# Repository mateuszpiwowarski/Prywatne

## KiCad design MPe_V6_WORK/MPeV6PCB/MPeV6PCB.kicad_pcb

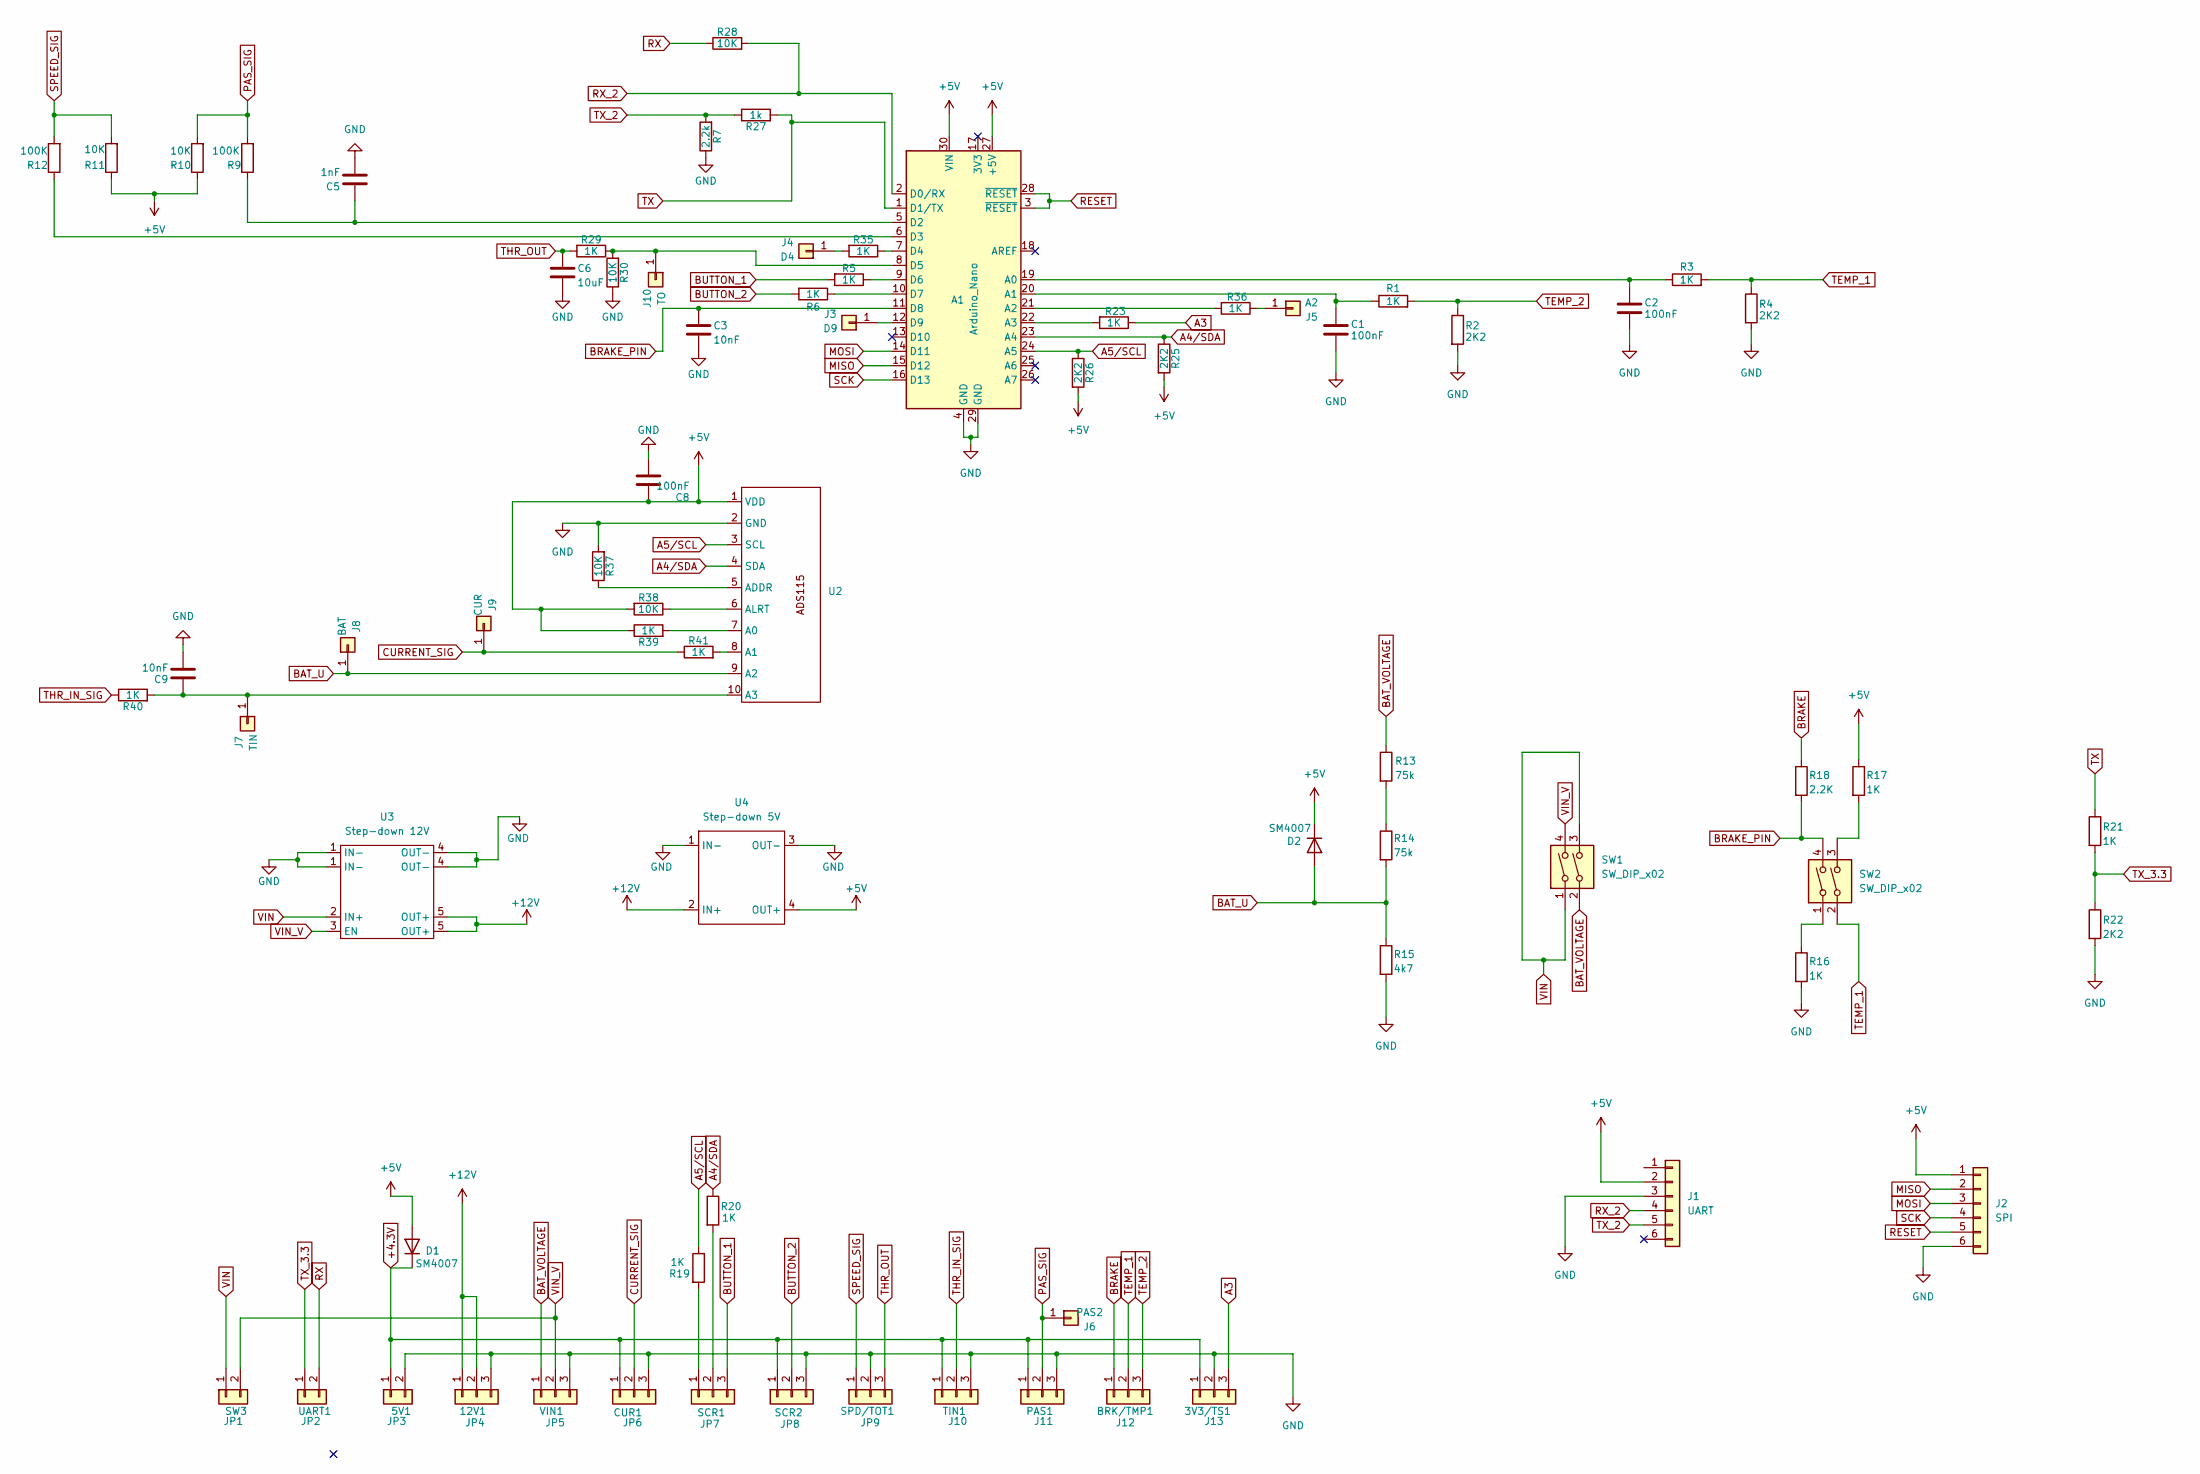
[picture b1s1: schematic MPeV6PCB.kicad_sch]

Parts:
3V3/TS1: J13; DG30825403P1400AH
5V1: JP3; DG30825402P1400AH
12V1: JP4; DG30825403P1400AH
A1: Arduino_Nano
BRK/TMP1: J12; DG30825403P1400AH
C1, C2, C8: 100nF; C_0603_1608Metric_Pad1.08x0.95mm_HandSolder
C3, C9: 10nF; C_0603_1608Metric_Pad1.08x0.95mm_HandSolder
C5: 1nF; C_0603_1608Metric_Pad1.08x0.95mm_HandSolder
C6: 10uF; C_0603_1608Metric_Pad1.08x0.95mm_HandSolder
CUR1: JP6; DG30825403P1400AH
D1, D2: SM4007; D_MELF
J1: UART; TerminalBlock_Xinya_XY308-2.54-6P_1x06_P2.54mm_Horizontal
J2: SPI; TerminalBlock_Xinya_XY308-2.54-6P_1x06_P2.54mm_Horizontal
J3: D9; HOLE
J4: D4; HOLE
J5: A2; HOLE
J6: PAS2; HOLE
J7: TIN; HOLE
J8: BAT; HOLE
J9: CUR; HOLE
J10: TO; HOLE
PAS1: J11; DG30825403P1400AH
R1, R3, R5, R6, R16, R17, R19, R20, R21, R23, R29, R35, R36, R39, R40, R41: 1K; R_0805_2012Metric_Pad1.20x1.40mm_HandSolder
R2, R4, R22, R25, R26: 2K2; R_0805_2012Metric_Pad1.20x1.40mm_HandSolder
R7: 2.2k; R_0805_2012Metric_Pad1.20x1.40mm_HandSolder
R9, R12: 100K; R_0805_2012Metric_Pad1.20x1.40mm_HandSolder
R10, R11, R28, R30, R37, R38: 10K; R_0805_2012Metric_Pad1.20x1.40mm_HandSolder
R13, R14: 75k; R_0805_2012Metric_Pad1.20x1.40mm_HandSolder
R15: 4k7; R_0805_2012Metric_Pad1.20x1.40mm_HandSolder
R18: 2.2K; R_0805_2012Metric_Pad1.20x1.40mm_HandSolder
R27: 1k; R_0805_2012Metric_Pad1.20x1.40mm_HandSolder
SCR1: JP7; DG30825403P1400AH
SCR2: JP8; DG30825403P1400AH
SPD/TOT1: JP9; DG30825403P1400AH
SW1, SW2: SW_DIP_x02; SW_DIP_SPSTx02_Slide_9.78x7.26mm_W7.62mm_P2.54mm
SW3: JP1; DG30825402P1400AH
TIN1: J10; DG30825403P1400AH
U2: ADS1115PCB
U3: Step-down 12V; 12V Step-Down
U4: Step-down 5V; 5V Step-Down
UART1: JP2; DG30825402P1400AH
VIN1: JP5; DG30825403P1400AH

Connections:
+4.3V: 3V3/TS1.1, 5V1.1, CUR1.1, D1.1 (K), PAS1.1, SCR2.1, TIN1.1
+5V: A1.27 (+5V), A1.30 (VIN), C8.1, D1.2 (A), D2.1 (K), J1.2, J2.1, R10.1, R11.1, R17.1, R25.2, R26.2, R38.2, R39.1, U2.1 (VDD), U4.4 (OUT+)
+12V: 12V1.1, 12V1.2, U3.5 (OUT+), U4.2 (IN+)
A3: 3V3/TS1.3, R23.1
A4/SDA: A1.23 (A4), R20.1, R25.1, U2.4 (SDA)
A5/SCL: A1.24 (A5), R19.1, R26.1, U2.3 (SCL)
BAT_U: D2.2 (A), J8.1, R14.2, R15.1, U2.9 (A2)
BAT_VOLTAGE: R13.1, SW1.2, VIN1.1
BRAKE: BRK/TMP1.1, R18.1
BRAKE_PIN: A1.11 (D8), C3.1, R18.2, SW2.4
BUTTON_1: R5.2, SCR1.3
BUTTON_2: R6.2, SCR2.2
CURRENT_SIG: CUR1.2, J9.1, R41.1
GND: 3V3/TS1.2, 5V1.2, 12V1.3, A1.4 (GND), A1.29 (GND), C1.2, C2.2, C3.2, C5.2, C6.2, C8.2, C9.2, CUR1.3, J1.3, J2.6, PAS1.3, R2.2, R4.2, R7.1, R15.2, R16.2, R22.2, R30.1, R37.2, SCR2.3, SPD/TOT1.2, TIN1.3, U2.2 (GND), U3.1 (IN-), U3.4 (OUT-), U4.1 (IN-), U4.3 (OUT-), VIN1.3
MISO: A1.15 (D12), J2.2
MOSI: A1.14 (D11), J2.3
unnamed: A1.19 (A0), C2.1, R3.1
unnamed: A1.20 (A1), C1.1, R1.1
unnamed: A1.21 (A2), R36.2
unnamed: A1.22 (A3), R23.2
unnamed: A1.5 (D2), C5.1, R9.1
unnamed: A1.6 (D3), R12.1
unnamed: A1.7 (D4), R35.1
unnamed: A1.8 (D5), J10.1, R29.1, R30.2
unnamed: A1.9 (D6), R5.1
unnamed: A1.10 (D7), R6.1
unnamed: A1.12 (D9), J3.1
unnamed: J4.1, R35.2
unnamed: J5.1, R36.1
unnamed: C9.1, J7.1, R40.2, U2.10 (A3)
unnamed: R13.2, R14.1
unnamed: R16.1, SW2.1
unnamed: R17.2, SW2.3
unnamed: R19.2, SCR1.1
unnamed: R20.2, SCR1.2
unnamed: R39.2, U2.7 (A0)
unnamed: R41.2, U2.8 (A1)
unnamed: R37.1, U2.5 (ADDR)
unnamed: R38.1, U2.6 (ALRT)
PAS_SIG: J6.1, PAS1.2, R9.2, R10.2
RESET: A1.3 (~RESET), A1.28 (~RESET), J2.5
RX: R28.1, UART1.2
RX_2: A1.2 (D0/RX), J1.4, R28.2
SCK: A1.16 (D13), J2.4
SPEED_SIG: R11.2, R12.2, SPD/TOT1.1
TEMP_1: BRK/TMP1.2, R3.2, R4.1, SW2.2
TEMP_2: BRK/TMP1.3, R1.2, R2.1
THR_IN_SIG: R40.1, TIN1.2
THR_OUT: C6.1, R29.2, SPD/TOT1.3
TX: A1.1 (D1/TX), R21.1, R27.2
TX_2: J1.5, R7.2, R27.1
TX_3.3: R21.2, R22.1, UART1.1
VIN: SW1.1, SW1.3, SW3.1, U3.2 (IN+)
VIN_V: SW1.4, SW3.2, U3.3 (EN), VIN1.2

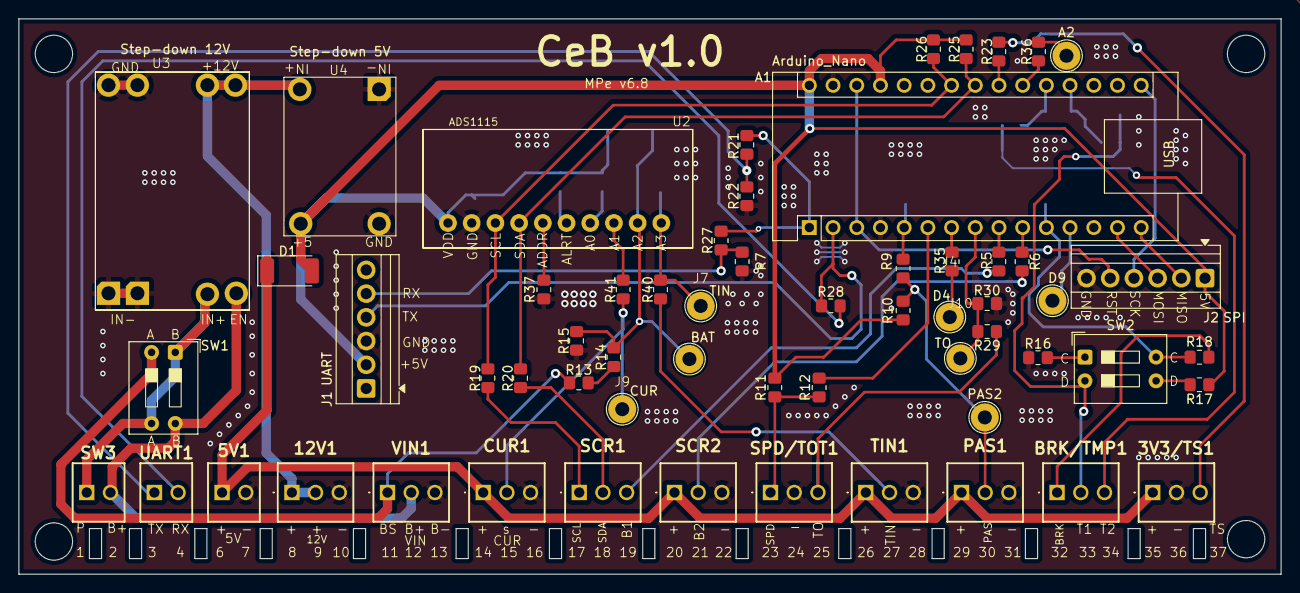
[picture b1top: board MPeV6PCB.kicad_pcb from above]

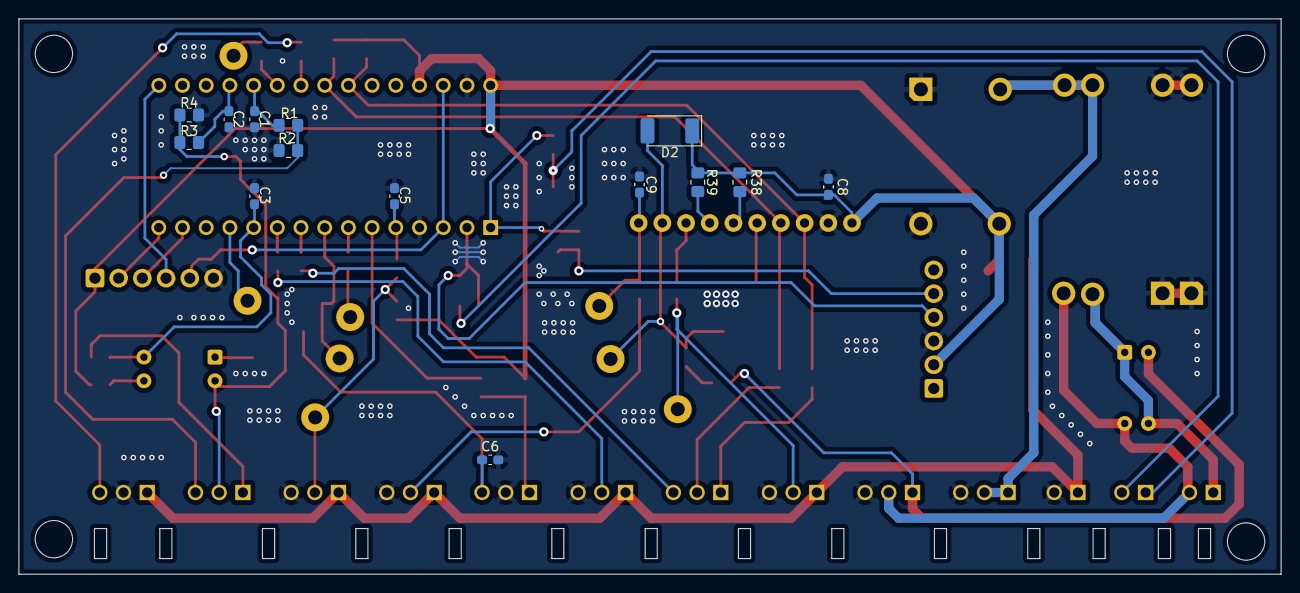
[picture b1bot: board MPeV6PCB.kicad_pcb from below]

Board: 2 copper layers, 135.2 x 59.5 mm, 73 parts (14 on the bottom side), 54 nets.

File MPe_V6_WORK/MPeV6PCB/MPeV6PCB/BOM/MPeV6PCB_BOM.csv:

"sep=;"
Id;Designator;Footprint;Quantity;Value;Supplier and ref
1;3V3/TS1;SamacSys_Parts:DG30825403P1400AH;1;J13;
2;5V1;SamacSys_Parts:DG30825402P1400AH;1;JP3;
3;12V1;SamacSys_Parts:DG30825403P1400AH;1;JP4;
4;A1;Module:Arduino_Nano;1;Arduino_Nano;
5;BRK/TMP1;SamacSys_Parts:DG30825403P1400AH;1;J12;
6;C1,C2,C8;Capacitor_SMD:C_0603_1608Metric_Pad1.08x0.95mm_HandSolder;3;100nF;
7;C3,C9;Capacitor_SMD:C_0603_1608Metric_Pad1.08x0.95mm_HandSolder;2;10nF;
8;C5;Capacitor_SMD:C_0603_1608Metric_Pad1.08x0.95mm_HandSolder;1;1nF;
9;C6;Capacitor_SMD:C_0603_1608Metric_Pad1.08x0.95mm_HandSolder;1;10uF;
10;CUR1;SamacSys_Parts:DG30825403P1400AH;1;JP6;
11;D1,D2;Diode_SMD:D_MELF;2;SM4007;
12;J1;TerminalBlock:TerminalBlock_Xinya_XY308-2.54-6P_1x06_P2.54mm_Horizontal;1;UART;
13;J2;TerminalBlock:TerminalBlock_Xinya_XY308-2.54-6P_1x06_P2.54mm_Horizontal;1;SPI;
14;J3;New_Library_Footprint:HOLE;1;D9;
15;J4;New_Library_Footprint:HOLE;1;D4;
16;J5;New_Library_Footprint:HOLE;1;A2;
17;J6;New_Library_Footprint:HOLE;1;PAS2;
18;J7;New_Library_Footprint:HOLE;1;TIN;
19;J8;New_Library_Footprint:HOLE;1;BAT;
20;J9;New_Library_Footprint:HOLE;1;CUR;
21;J10;New_Library_Footprint:HOLE;1;TO;
22;PAS1;SamacSys_Parts:DG30825403P1400AH;1;J11;
23;R1,R3,R5,R6,R16,R17,R19-R21,R23,R29,R35,R36,R39-R41;Resistor_SMD:R_0805_2012Metric_Pad1.20x1.40mm_HandSolder;16;1K;
24;R2,R4,R22,R25,R26;Resistor_SMD:R_0805_2012Metric_Pad1.20x1.40mm_HandSolder;5;2K2;
25;R7;Resistor_SMD:R_0805_2012Metric_Pad1.20x1.40mm_HandSolder;1;2.2k;
26;R9,R12;Resistor_SMD:R_0805_2012Metric_Pad1.20x1.40mm_HandSolder;2;100K;
27;R10,R11,R28,R30,R37,R38;Resistor_SMD:R_0805_2012Metric_Pad1.20x1.40mm_HandSolder;6;10K;
28;R13,R14;Resistor_SMD:R_0805_2012Metric_Pad1.20x1.40mm_HandSolder;2;75k;
29;R15;Resistor_SMD:R_0805_2012Metric_Pad1.20x1.40mm_HandSolder;1;4k7;
30;R18;Resistor_SMD:R_0805_2012Metric_Pad1.20x1.40mm_HandSolder;1;2.2K;
31;R27;Resistor_SMD:R_0805_2012Metric_Pad1.20x1.40mm_HandSolder;1;1k;
32;SCR1;SamacSys_Parts:DG30825403P1400AH;1;JP7;
33;SCR2;SamacSys_Parts:DG30825403P1400AH;1;JP8;
34;SPD/TOT1;SamacSys_Parts:DG30825403P1400AH;1;JP9;
35;SW1,SW2;Button_Switch_THT:SW_DIP_SPSTx02_Slide_9.78x7.26mm_W7.62mm_P2.54mm;2;SW_DIP_x02;
36;SW3;SamacSys_Parts:DG30825402P1400AH;1;JP1;
37;TIN1;SamacSys_Parts:DG30825403P1400AH;1;J10;
38;U2;New_Library_Footprint:ADS1115PCB;1;~;
39;U3;New_Library_Footprint:12V Step-Down;1;Step-down 12V;
40;U4;New_Library_Footprint:5V Step-Down;1;Step-down 5V;
41;UART1;SamacSys_Parts:DG30825402P1400AH;1;JP2;
42;VIN1;SamacSys_Parts:DG30825403P1400AH;1;JP5;

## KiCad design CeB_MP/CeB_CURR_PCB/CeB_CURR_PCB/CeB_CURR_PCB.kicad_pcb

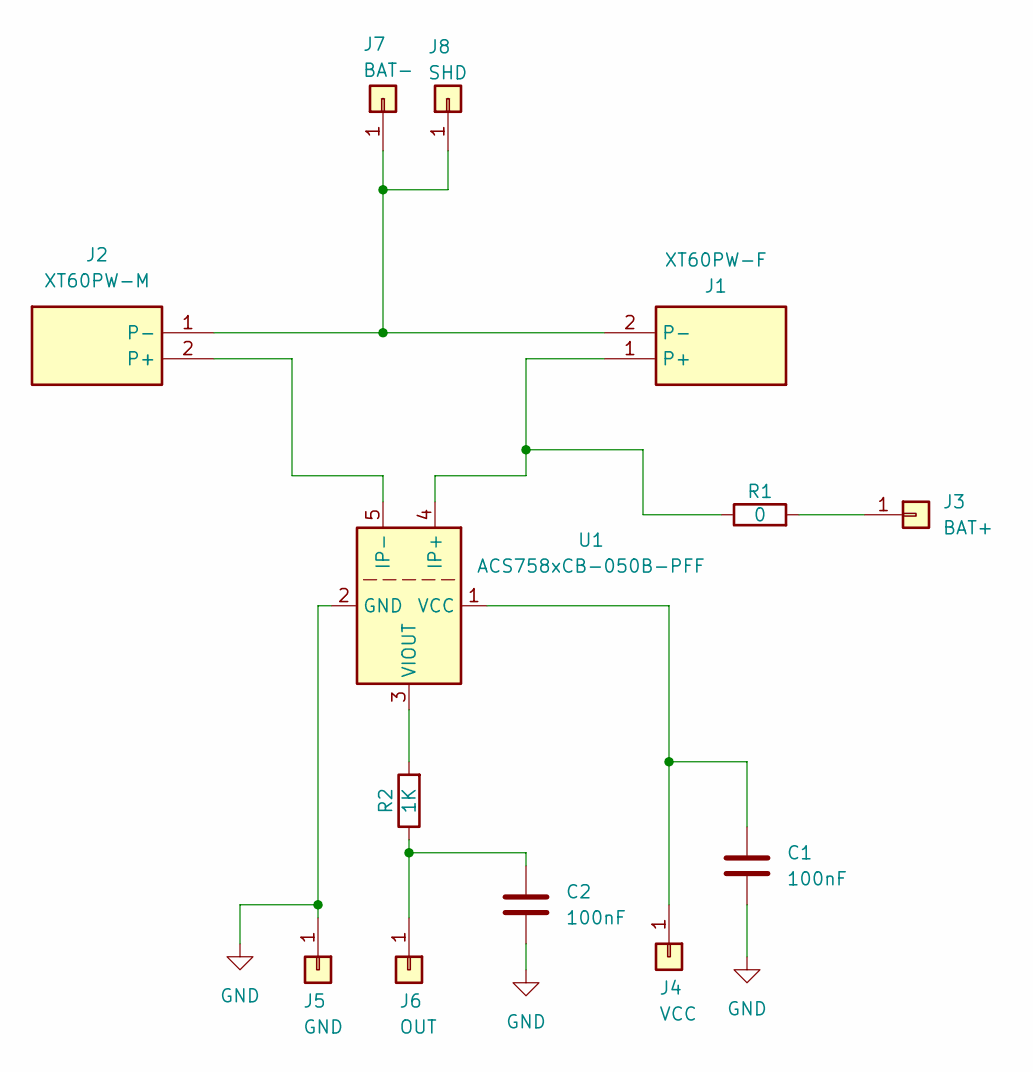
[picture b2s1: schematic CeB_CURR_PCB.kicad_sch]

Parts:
C1, C2: 100nF; C_0603_1608Metric_Pad1.08x0.95mm_HandSolder
J1: XT60PW-F; XT60PWF; Manufacturer_Part_Number XT60PW-F
J2: XT60PW-M; XT60PWM; Manufacturer_Part_Number XT60PW-M
J3: BAT+; HOLE
J4: VCC; HOLE
J5: GND; HOLE
J6: OUT; HOLE
J7: BAT-; HOLE
J8: SHD; HOLE
R1: 0; R_0603_1608Metric_Pad0.98x0.95mm_HandSolder
R2: 1K; R_0603_1608Metric_Pad0.98x0.95mm_HandSolder
U1: ACS758xCB-050B-PFF; Allegro_CB_PFF

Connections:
GND: C1.2, C2.2, J5.1, U1.2 (GND)
unnamed: J1.1 (P+), R1.1, U1.4 (IP+)
unnamed: J1.2 (P-), J2.1 (P-), J7.1, J8.1
unnamed: J2.2 (P+), U1.5 (IP-)
unnamed: J3.1, R1.2
unnamed: C1.1, J4.1, U1.1 (VCC)
unnamed: C2.1, J6.1, R2.1
unnamed: R2.2, U1.3 (VIOUT)

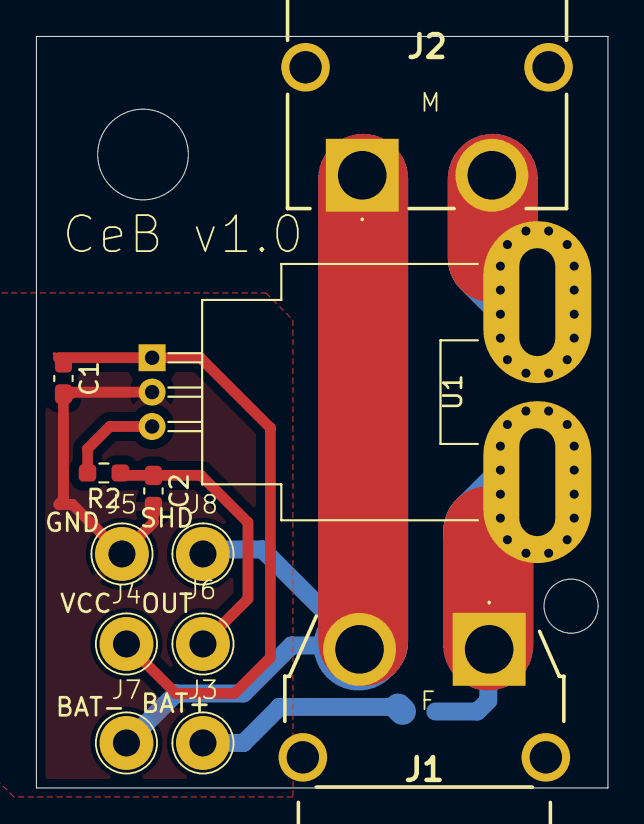
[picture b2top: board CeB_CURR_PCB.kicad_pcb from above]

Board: 2 copper layers, 31.8 x 41.8 mm, 13 parts (1 on the bottom side), 8 nets.

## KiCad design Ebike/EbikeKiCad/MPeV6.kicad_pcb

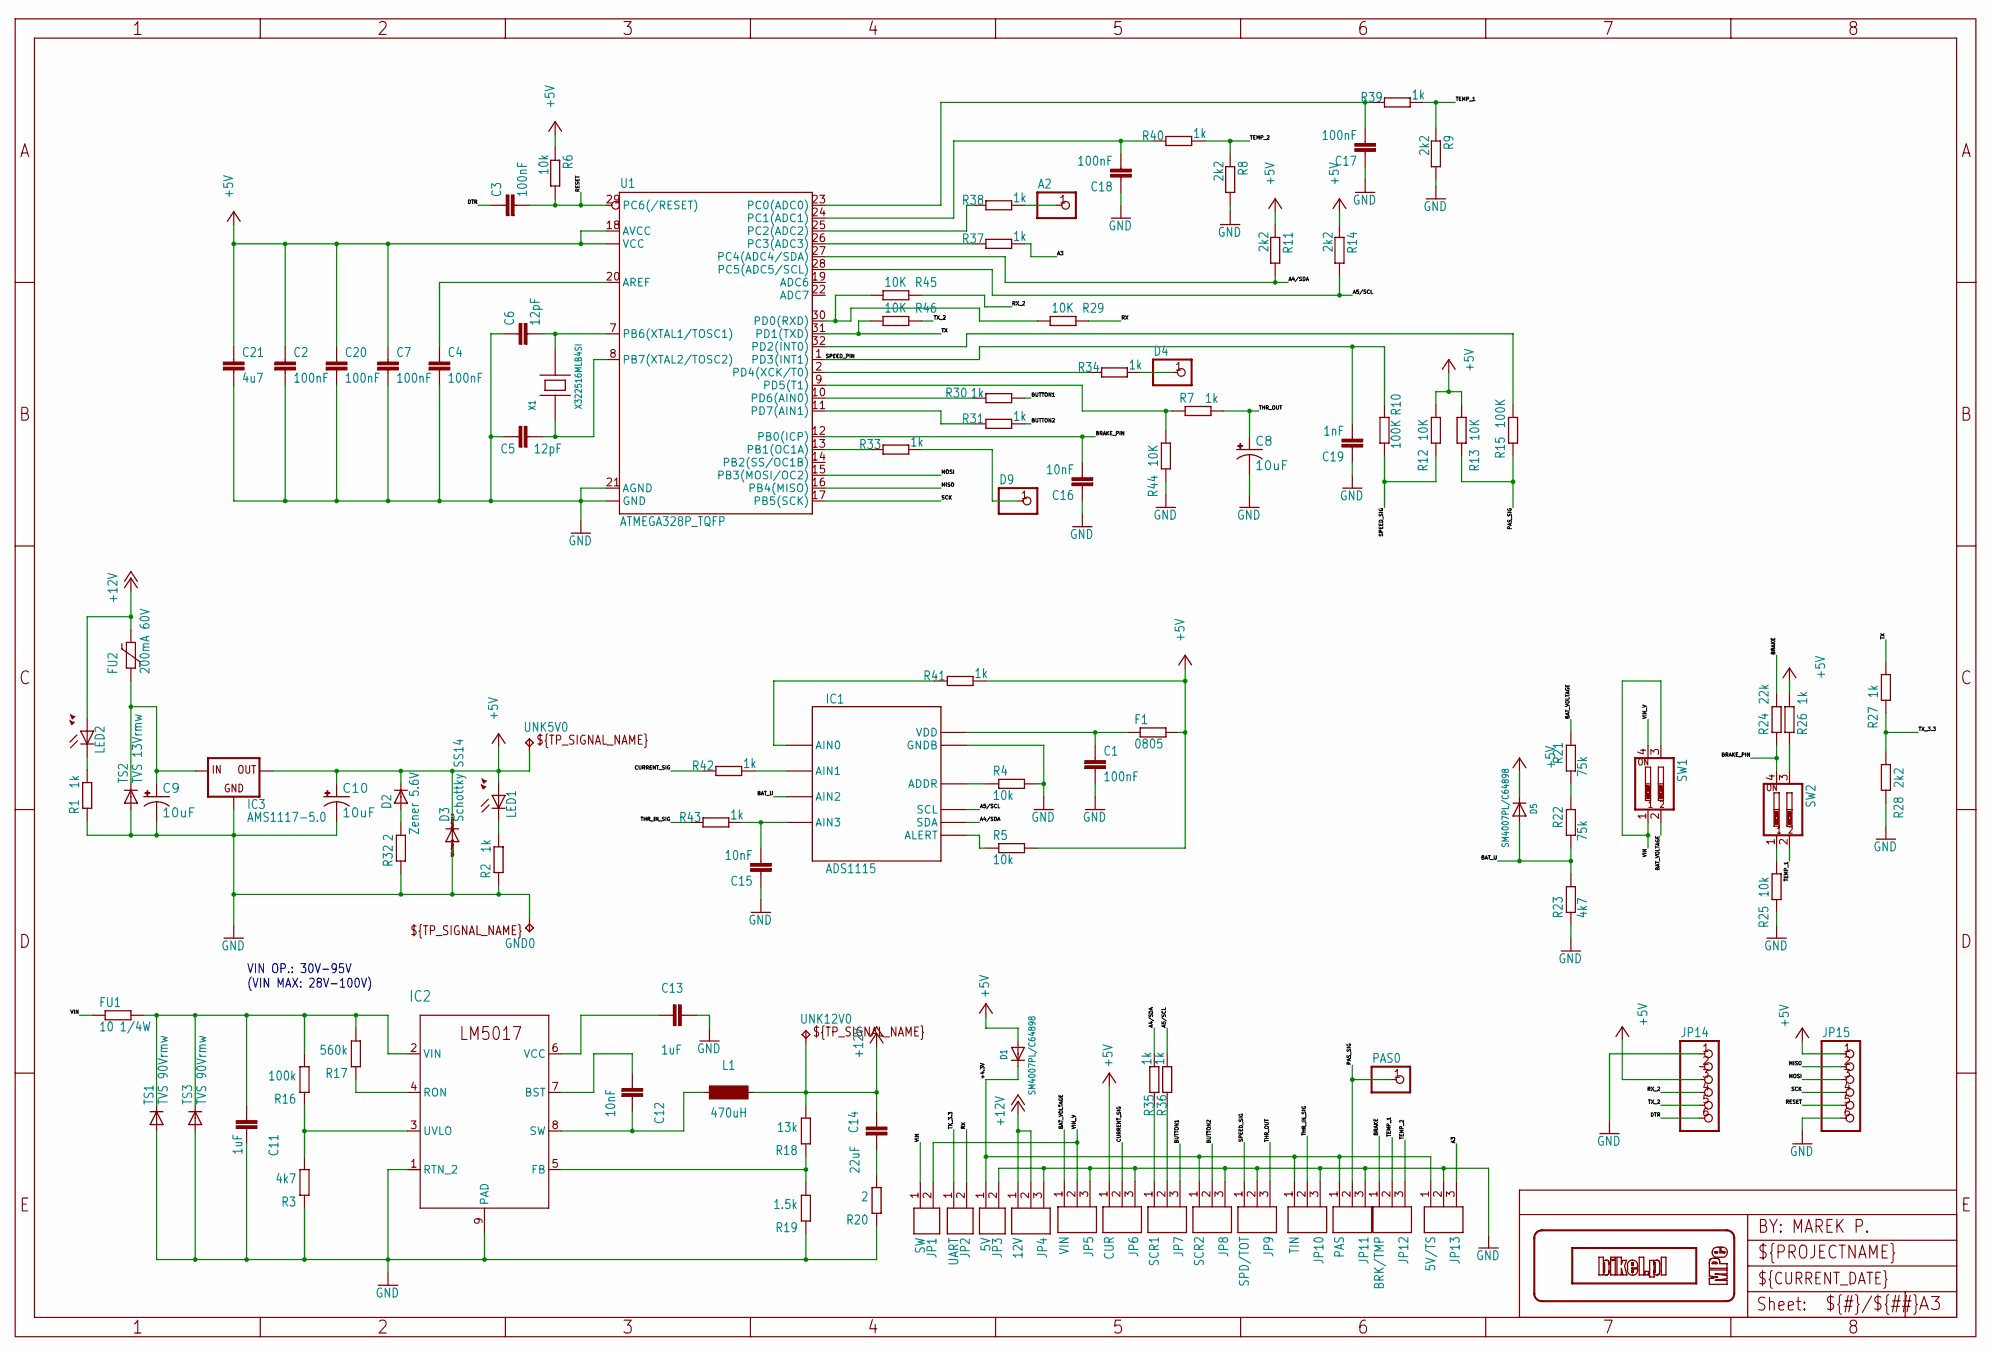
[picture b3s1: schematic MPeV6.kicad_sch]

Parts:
A2: PINHD-1X1; 1X01
C1, C2, C3, C4, C7, C17, C18, C20: 100nF; C0603
C5, C6: 12pF; C0603
C8, C9, C10: 10uF; EIA3216
C11: 1uF; C1206
C12: 10nF; C0805
C13: 1uF; C0603
C14: 22uF; C0805
C15, C16: 10nF; C0603
C19: 1nF; C0603
C21: 4u7; C0603
D1, D5: SM4007PL/C64898; SOD-123
D2: Zener 5.6V; MELF-MLL34
D3: Schottky SS14; DO-214AC
D4, D9: PINHD-1X1; 1X01
F1: 0805; R0805
FU1: 10 1/4W; 0204_7
FU2: 200mA 60V; 1812L
GND0: TP_5V; P1-13
IC1: ADS1115; MSOP10_0.5
IC2: LM5017MR/NOPB; MRA08A
IC3: AMS1117-5.0; SOT223
JP1: SW; ARK254-PB+
JP2: UART; ARK254-2-COM
JP3: 5V; ARK254-2-5V
JP4: 12V; ARK254-3-12V-EL
JP5: VIN; ARK254-3-VIN
JP6: CUR; ARK254-3+S-
JP7: SCR1; ARK254-3
JP8: SCR2; ARK254-3
JP9: SPD/TOT; ARK254-3-SPD-TOT
JP10: TIN; ARK254-3+S-
JP11: PAS; ARK254-3+S-
JP12: BRK/TMP; ARK254-3-BRK-TMP
JP13: 5V/TS; ARK254-3-5V-TS
JP14, JP15: PINHD-1X6; 1X06
L1: 470uH; SLF12555T-102MR34-PF; LCSC C13738
LED1, LED2: LEDCHIP-LED0805; CHIP-LED0805
PAS0: PINHD-1X1; 1X01
R1, R2, R7, R26, R27, R30, R31, R33, R34, R35, R36, R37, R38, R39, R40, R41, R42, R43: 1k; R0603
R3: 4k7; R0603
R4, R5, R6, R25: 10k; R0603
R8, R9, R11, R14, R28: 2k2; R0603
R10, R15: 100K; R0603
R12, R13, R29, R44, R45, R46: 10K; R0603
R16: 100k; R0603
R17: 560k; R0603
R18: 13k; R0603
R19: 1.5k; R0603
R20, R32: 2; R0805
R21, R22: 75k; R0805
R23: 4k7; R0805
R24: 22k; R0603
SW1, SW2: SW_DIP-2; EDG-02
TS1, TS3: TVS 90Vrmw; DO214AA
TS2: TVS 13Vrmw; DO214AA
U1: ATMEGA328P_TQFP; TQFP32-08
UNK5V0, UNK12V0: TP_5V; P1-13
X1: X322516MLB4SI; IQG3225

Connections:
3: IC2.5 (FB), R18.2, R19.1
6: C13.2, IC2.6 (VCC)
7: IC2.4 (RON), R17.2
9: C14.2, R20.1
12V_FUSED: C9.+, FU2.2, IC3.3 (IN), TS2.C
+4.3V: D1.C, JP3.1, JP8.1, JP10.1, JP11.1, JP13.1
+5V: C2.1, C7.1, C10.+, C20.1, C21.1, D1.A, D2.1 (C), D3.C, D5.C, F1.2, IC3.2 (OUT), IC3.4 (OUT), JP6.1, JP14.3, JP15.1, LED1.A, R5.2, R6.1, R11.1, R12.2, R13.2, R14.1, R26.2, R41.1, U1.4 (VCC), U1.6 (VCC), U1.18 (AVCC), UNK5V0.TP; also elsewhere on the board
+12V: C14.1, FU2.1, JP4.1, JP4.2, L1.P$2 (2), LED2.A, R18.1, UNK12V0.TP; also elsewhere on the board
A2: R38.2, U1.25 (PC2(ADC2))
A3: JP13.3, R37.1
A4/SDA: IC1.9 (SDA), R11.2, R35.1, U1.27 (PC4(ADC4/SDA))
A5/SCL: IC1.10 (SCL), R14.2, R36.1, U1.28 (PC5(ADC5/SCL))
BAT_U: D5.A, IC1.6 (AIN2), R22.1, R23.2
BAT_VOLTAGE: JP5.1, R21.2, SW1.2
BRAKE: JP12.1, R24.2
BRAKE_PIN: C16.2, R24.1, SW2.4, U1.12 (PB0(ICP))
BUTTON1: JP7.3, R30.1
BUTTON2: JP8.2, R31.1
CSIG: IC1.5 (AIN1), R42.1
CURRENT_SIG: JP6.2, R42.2
DTR: C3.1, JP14.6
GND: C1.2, C2.2, C4.2, C5.1, C6.1, C7.2, C8.-, C9.-, C10.-, C11.2, C13.1, C15.1, C16.1, C17.1, C18.1, C19.1, C20.2, C21.2, D3.A, GND0.TP, IC1.3 (GNDB), IC2.1 (RTN_2), IC2.9 (PAD), IC3.1 (GND), JP3.2, JP4.3, JP5.3, JP6.3, JP8.3, JP9.2, JP10.3, JP11.3, JP13.2, JP14.1, JP15.6, R1.1, R2.1, R3.2, R4.2, R8.2, R9.2, R19.2, R20.2, R23.1, R25.1, R28.1, R32.1, R44.1, TS1.A, TS2.A, TS3.A, U1.3 (GND), U1.5 (GND), U1.21 (AGND); also elsewhere on the board
MISO: JP15.2, U1.16 (PB4(MISO))
MOSI: JP15.3, U1.15 (PB3(MOSI/OC2))
unnamed: LED1.C, R2.2
unnamed: JP7.1, R35.2
unnamed: IC2.3 (UVLO), R3.1, R16.2
unnamed: JP7.2, R36.2
unnamed: D9.1, R33.1
unnamed: C12.1, IC2.7 (BST)
unnamed: R7.1, R44.2, U1.9 (PD5(T1))
unnamed: C4.1, U1.20 (AREF)
unnamed: LED2.C, R1.2
unnamed: R15.2, U1.32 (PD2(INT0))
unnamed: IC1.1 (ADDR), R4.1
unnamed: IC1.2 (ALERT), R5.1
unnamed: D4.1, R34.1
unnamed: IC1.4 (AIN0), R41.2
unnamed: R29.2, R45.2, U1.30 (PD0(RXD))
unnamed: D2.2 (A), R32.2
unnamed: R25.2, SW2.1
unnamed: R30.2, U1.10 (PD6(AIN0))
unnamed: R31.2, U1.11 (PD7(AIN1))
unnamed: R26.1, SW2.3
unnamed: C11.1, FU1.2, IC2.2 (VIN), R16.1, R17.1, TS1.C, TS3.C
unnamed: R33.2, U1.13 (PB1(OC1A))
unnamed: R34.2, U1.2 (PD4(XCK/T0))
unnamed: C6.2, U1.7 (PB6(XTAL1/TOSC1)), X1.3 (PIN2)
unnamed: C5.2, U1.8 (PB7(XTAL2/TOSC2)), X1.1 (PIN1)
unnamed: R21.1, R22.2
unnamed: R37.2, U1.26 (PC3(ADC3))
unnamed: A2.1, R38.1
PAS_SIG: JP11.2, PAS0.1, R13.1, R15.1; also elsewhere on the board
RESET: C3.2, JP15.5, R6.2, U1.29 (PC6(/RESET))
RX: JP2.2, R29.1
RX_2: JP14.4, R45.1
SCK: JP15.4, U1.17 (PB5(SCK))
SPEED_PIN: C19.2, R10.2, U1.1 (PD3(INT1))
SPEED_SIG: JP9.1, R10.1, R12.1
SW: C12.2, IC2.8 (SW), L1.P$1 (1)
T1: C17.2, R39.2, U1.23 (PC0(ADC0))
T2: C18.2, R40.2, U1.24 (PC1(ADC1))
TEMP_1: JP12.2, R9.1, R39.1, SW2.2
TEMP_2: JP12.3, R8.1, R40.1
THR_IN_SIG: JP10.2, R43.2
THR_OUT: C8.+, JP9.3, R7.2
TSIG: C15.2, IC1.7 (AIN3), R43.1
TX: R27.2, R46.2, U1.31 (PD1(TXD))
TX_2: JP14.5, R46.1
TX_3.3: JP2.1, R27.1, R28.2
VDD: C1.1, F1.1, IC1.8 (VDD)
VIN: FU1.1, JP1.1, SW1.1, SW1.3
VIN_V: JP1.2, JP5.2, SW1.4

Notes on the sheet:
VIN OP.: 30V-95V (VIN MAX: 28V-100V)

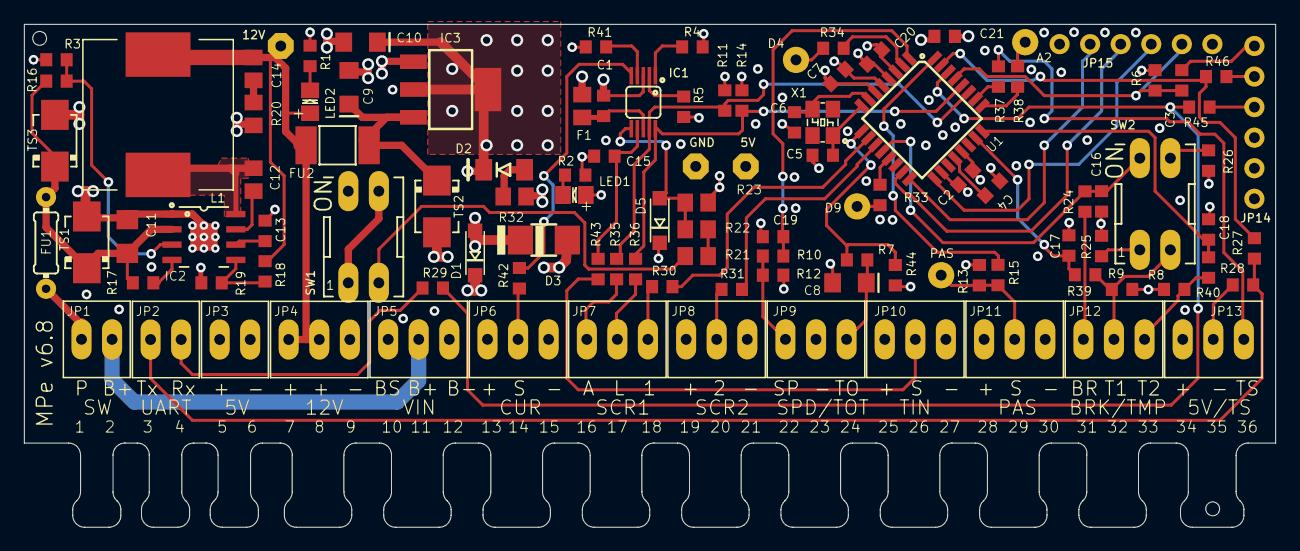
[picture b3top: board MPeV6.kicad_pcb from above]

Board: 4 copper layers, 104.0 x 41.8 mm, 111 parts (0 on the bottom side), 73 nets.

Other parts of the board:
5V, 12V: TP_5V; P1-13
GND: TP_5V; P1-13
PAS: 1X01
UNK_HOLE_0: dummyfp0
UNK_HOLE_1: dummyfp1

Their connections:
+5V: 5V.TP; also elsewhere on the board
+12V: 12V.TP; also elsewhere on the board
GND: GND.TP; also elsewhere on the board
PAS_SIG: PAS.1; also elsewhere on the board

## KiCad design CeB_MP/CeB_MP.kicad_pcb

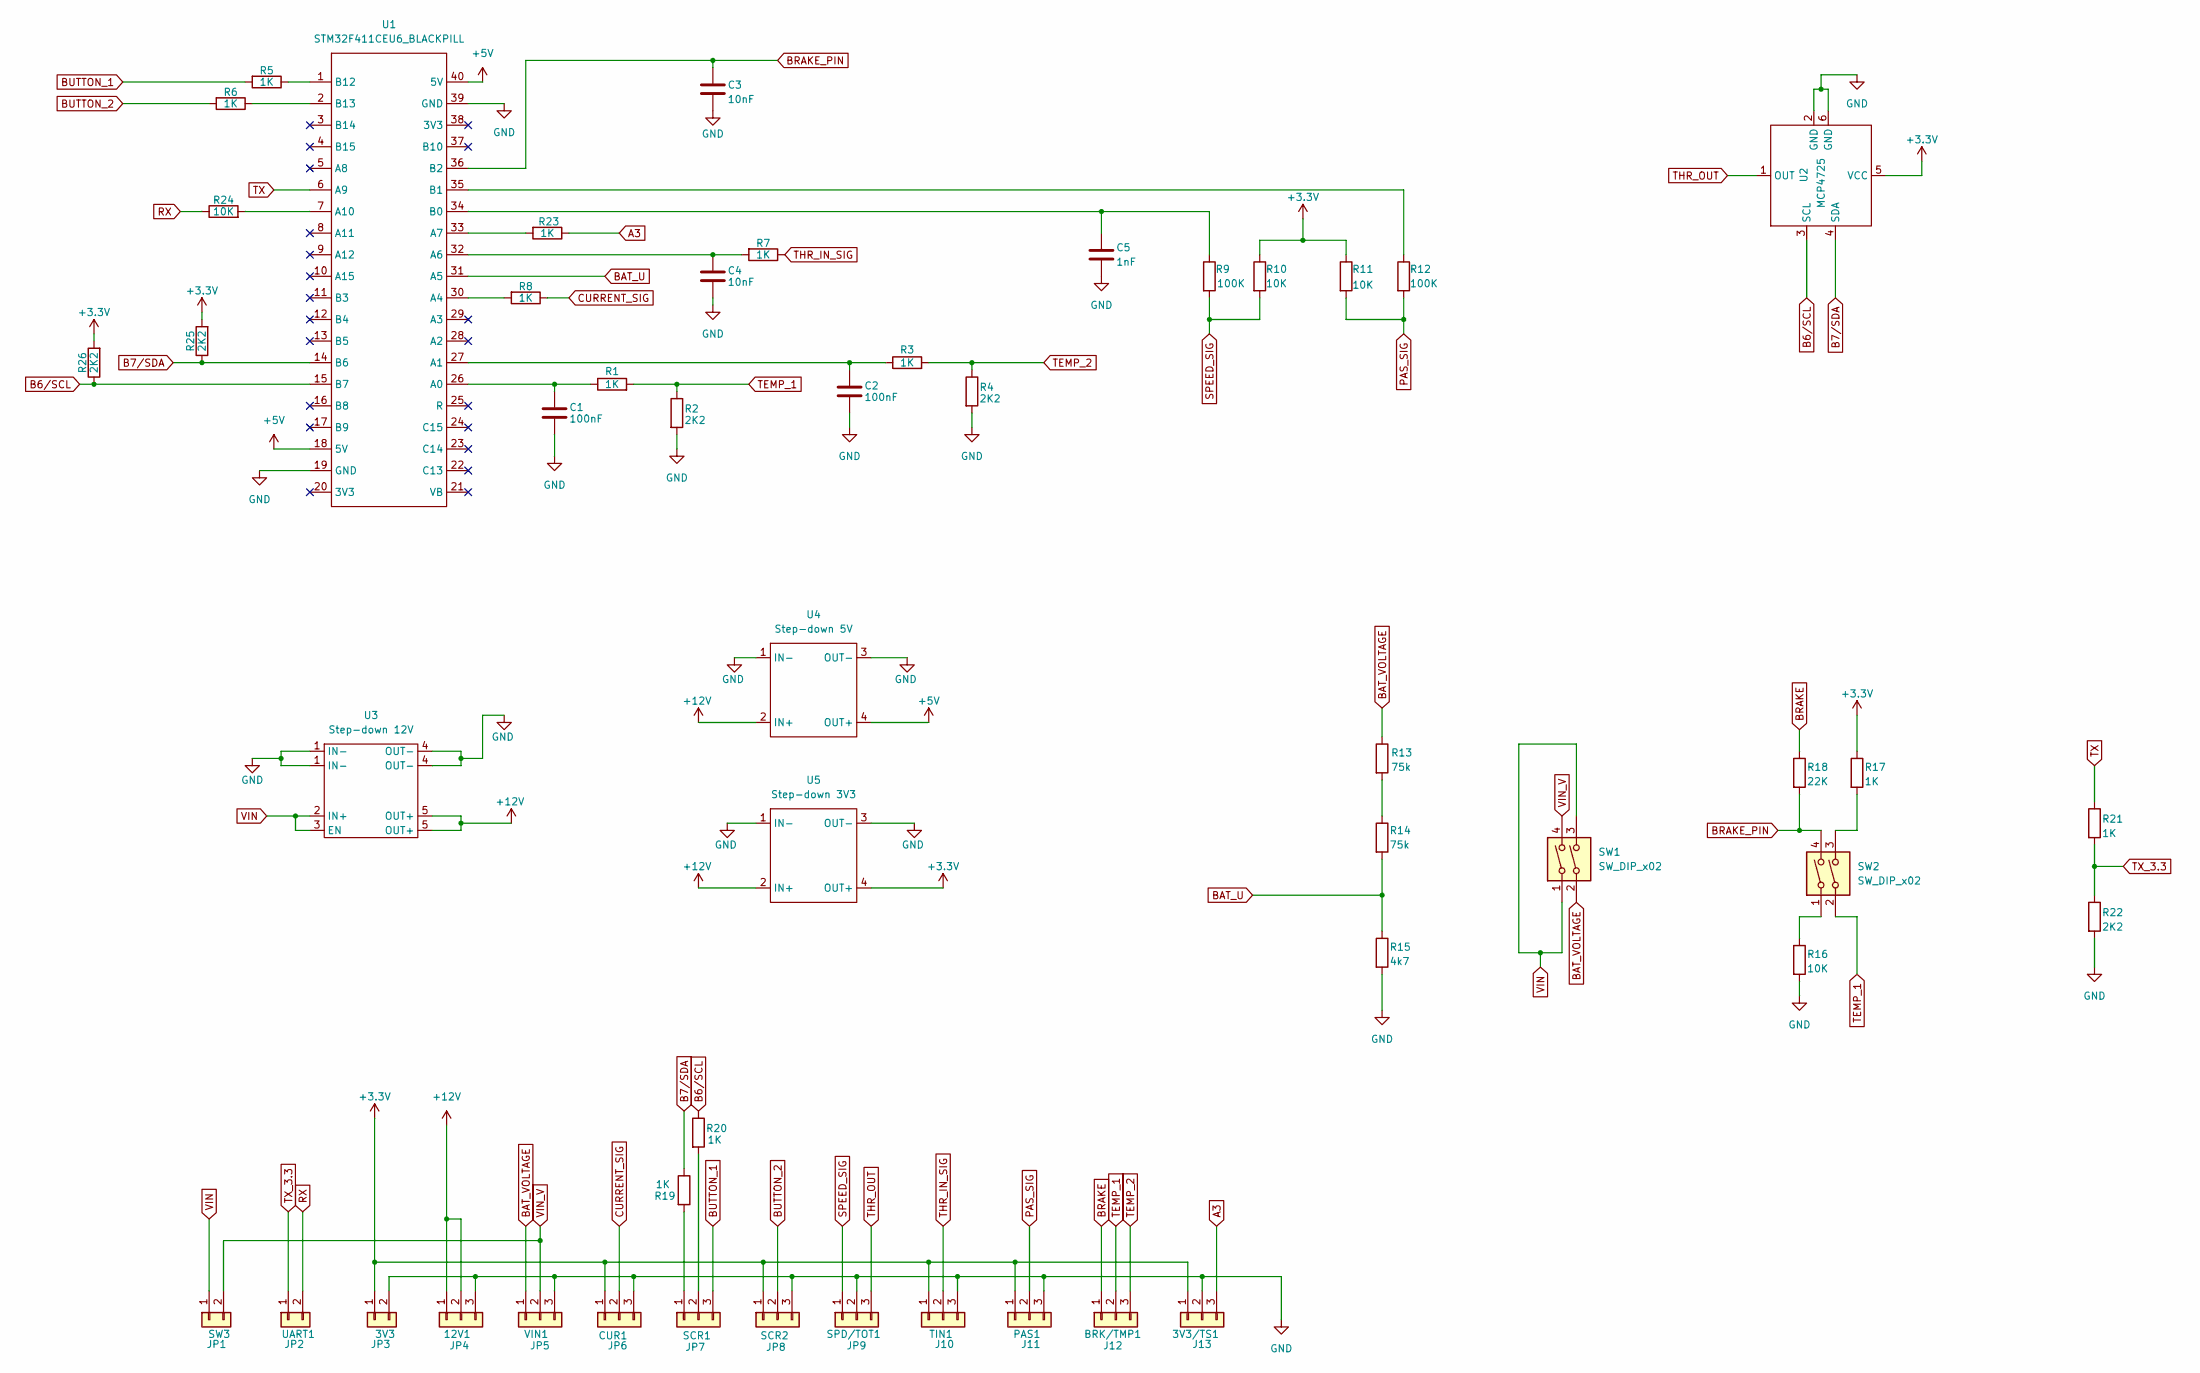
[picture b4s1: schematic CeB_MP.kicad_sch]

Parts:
3V3: JP3; DG30825402P1400AH
3V3/TS1: J13; DG30825403P1400AH
12V1: JP4; DG30825403P1400AH
BRK/TMP1: J12; DG30825403P1400AH
C1, C2: 100nF; C_0603_1608Metric_Pad1.08x0.95mm_HandSolder
C3, C4: 10nF; C_0603_1608Metric_Pad1.08x0.95mm_HandSolder
C5: 1nF; C_0603_1608Metric_Pad1.08x0.95mm_HandSolder
CUR1: JP6; DG30825403P1400AH
PAS1: J11; DG30825403P1400AH
R1, R3, R5, R6, R7, R8, R17, R19, R20, R21, R23: 1K; R_0805_2012Metric_Pad1.20x1.40mm_HandSolder
R2, R4, R22, R25, R26: 2K2; R_0805_2012Metric_Pad1.20x1.40mm_HandSolder
R9, R12: 100K; R_0805_2012Metric_Pad1.20x1.40mm_HandSolder
R10, R11, R16, R24: 10K; R_0805_2012Metric_Pad1.20x1.40mm_HandSolder
R13, R14: 75k; R_0805_2012Metric_Pad1.20x1.40mm_HandSolder
R15: 4k7; R_0805_2012Metric_Pad1.20x1.40mm_HandSolder
R18: 22K; R_0805_2012Metric_Pad1.20x1.40mm_HandSolder
SCR1: JP7; DG30825403P1400AH
SCR2: JP8; DG30825403P1400AH
SPD/TOT1: JP9; DG30825403P1400AH
SW1, SW2: SW_DIP_x02; SW_DIP_SPSTx02_Slide_9.78x7.26mm_W7.62mm_P2.54mm
SW3: JP1; DG30825402P1400AH
TIN1: J10; DG30825403P1400AH
U1: STM32F411CEU6_BLACKPILL
U2: MCP4725; MCP7525
U3: Step-down 12V; 12V Step-Down
U4: Step-down 5V; 5V Step-Down
U5: Step-down 3V3; 3V3 Step-Down
UART1: JP2; DG30825402P1400AH
VIN1: JP5; DG30825403P1400AH

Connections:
+3.3V: 3V3.1, 3V3/TS1.1, CUR1.1, PAS1.1, R10.1, R11.1, R17.1, R25.2, R26.2, SCR2.1, TIN1.1, U2.5 (VCC), U5.4 (OUT+)
+5V: U1.18 (5V), U1.40 (5V), U4.4 (OUT+)
+12V: 12V1.1, 12V1.2, U3.5 (OUT+), U4.2 (IN+), U5.2 (IN+)
A3: 3V3/TS1.3, R23.1
B6/SCL: R20.1, R26.1, U1.15 (B7), U2.3 (SCL)
B7/SDA: R19.1, R25.1, U1.14 (B6), U2.4 (SDA)
BAT_U: R14.2, R15.1, U1.31 (A5)
BAT_VOLTAGE: R13.1, SW1.2, VIN1.1
BRAKE: BRK/TMP1.1, R18.1
BRAKE_PIN: C3.1, R18.2, SW2.4, U1.36 (B2)
BUTTON_1: R5.2, SCR1.3
BUTTON_2: R6.2, SCR2.2
CURRENT_SIG: CUR1.2, R8.1
GND: 3V3.2, 3V3/TS1.2, 12V1.3, C1.2, C2.2, C3.2, C4.2, C5.2, CUR1.3, PAS1.3, R2.2, R4.2, R15.2, R16.2, R22.2, SCR2.3, SPD/TOT1.2, TIN1.3, U1.19 (GND), U1.39 (GND), U2.2 (GND), U2.6 (GND), U3.1 (IN-), U3.4 (OUT-), U4.1 (IN-), U4.3 (OUT-), U5.1 (IN-), U5.3 (OUT-), VIN1.3
unnamed: R13.2, R14.1
unnamed: R16.1, SW2.1
unnamed: R17.2, SW2.3
unnamed: R19.2, SCR1.1
unnamed: R20.2, SCR1.2
unnamed: C1.1, R1.1, U1.26 (A0)
unnamed: C2.1, R3.1, U1.27 (A1)
unnamed: R8.2, U1.30 (A4)
unnamed: C4.1, R7.2, U1.32 (A6)
unnamed: R23.2, U1.33 (A7)
unnamed: R24.2, U1.7 (A10)
unnamed: C5.1, R9.1, U1.34 (B0)
unnamed: R12.1, U1.35 (B1)
unnamed: R5.1, U1.1 (B12)
unnamed: R6.1, U1.2 (B13)
PAS_SIG: PAS1.2, R11.2, R12.2
RX: R24.1, UART1.2
SPEED_SIG: R9.2, R10.2, SPD/TOT1.1
TEMP_1: BRK/TMP1.2, R1.2, R2.1, SW2.2
TEMP_2: BRK/TMP1.3, R3.2, R4.1
THR_IN_SIG: R7.1, TIN1.2
THR_OUT: SPD/TOT1.3, U2.1 (OUT)
TX: R21.1, U1.6 (A9)
TX_3.3: R21.2, R22.1, UART1.1
VIN: SW1.1, SW1.3, SW3.1, U3.2 (IN+), U3.3 (EN)
VIN_V: SW1.4, SW3.2, VIN1.2

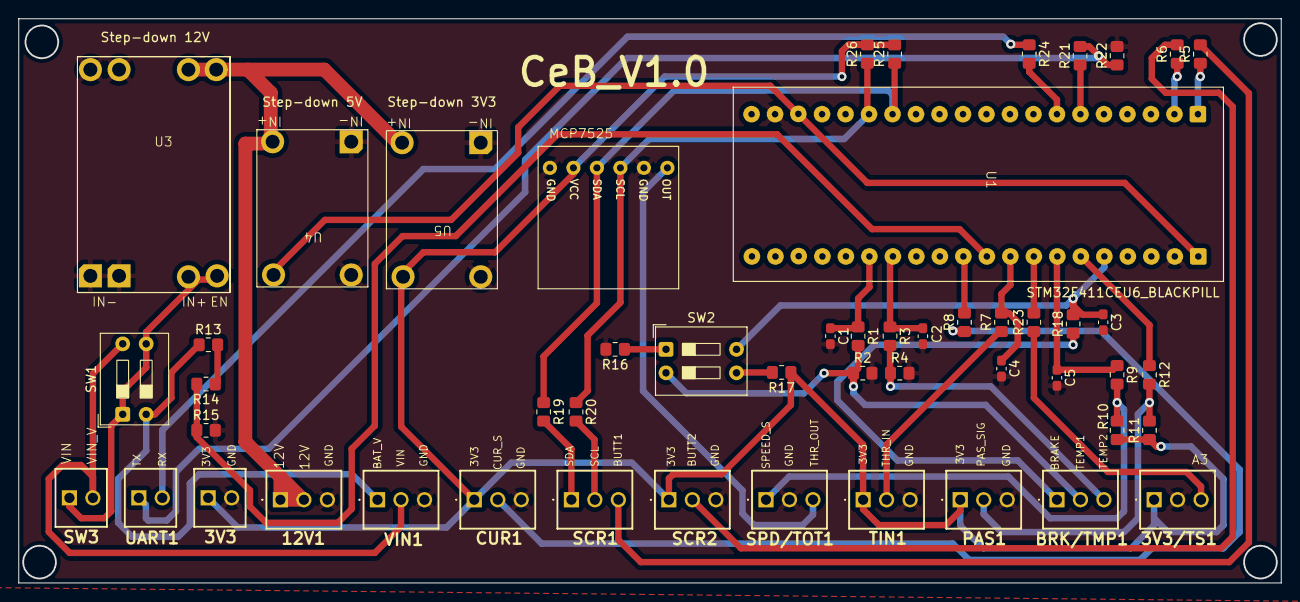
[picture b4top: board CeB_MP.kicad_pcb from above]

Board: 2 copper layers, 136.4 x 60.9 mm, 51 parts (0 on the bottom side), 40 nets.

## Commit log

2026-04-01 Pierwszy commit
2026-04-01 Tune X9C motor control behavior
2026-04-07 zmiana
2026-04-08 opis zmian
2026-04-08 Dodanie zmiany sterownaia na zyroskowpie
2026-04-12 Merge hoverboard and mower controller updates
    # Conflicts:
    # Kosiarka RC/Kosiarka sterowanie obrotami silnika (softstart)/src/main.cpp
2026-04-13 Move T2S temperature sensor to GPIO36
2026-04-13 Add non-blocking gyro assist bridge for hoverboard
2026-04-13 Refine mower gyro display and steering input
2026-04-13 Polish mower display layout and temp alerts
2026-04-13 Improve firmware resilience, profiles, and docs
2026-04-13 Stabilize speed sensor reading and OLED speed display
2026-04-14 Improve ELM responsiveness and BURN screen telemetry
2026-04-14 Update OBD2MODEL part design
2026-04-22 Add PlatformIO version of Dzialka Pomiar V
2026-04-22 Update Supla relay caption
2026-04-23 Restore Opel OBD platform to first commit
